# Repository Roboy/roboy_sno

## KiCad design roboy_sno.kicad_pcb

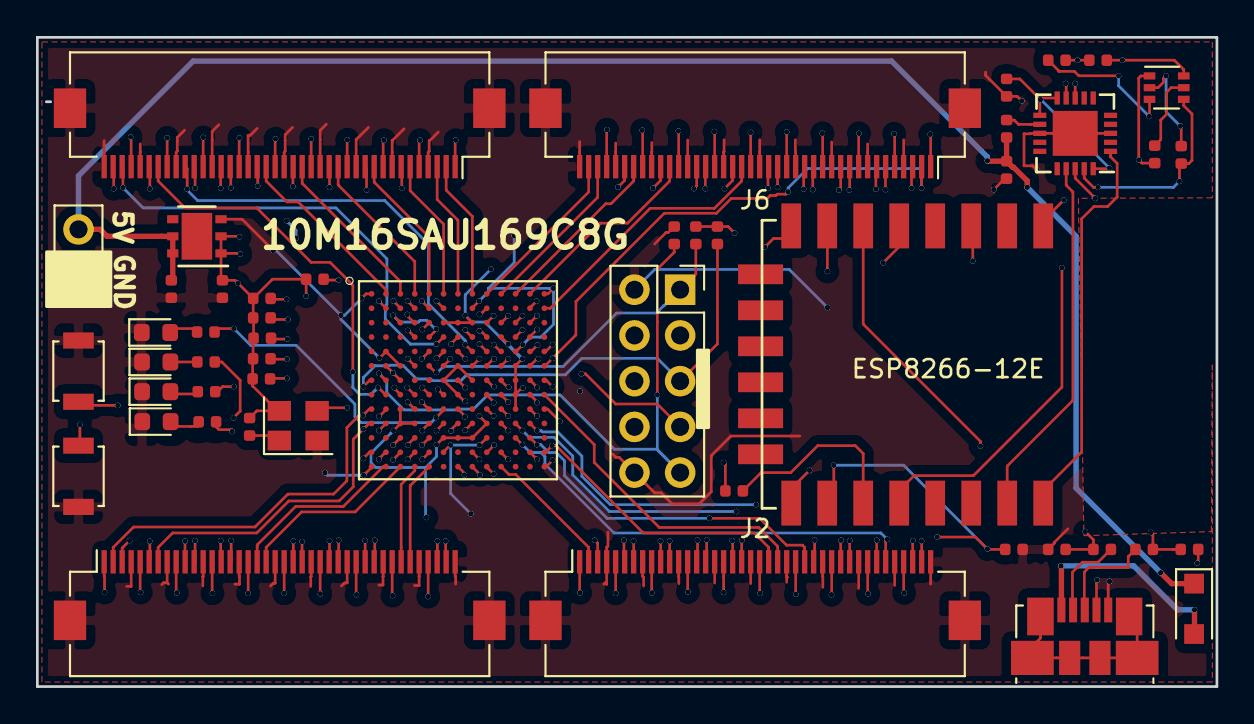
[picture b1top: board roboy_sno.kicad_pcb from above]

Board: 4 copper layers, 65.5 x 36.1 mm, 49 parts (0 on the bottom side), 126 nets.

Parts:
C2, C6: 10uF; C_0402_1005Metric
C8, C11: 47pF; C_0402_1005Metric
C9: 10n; C_0402_1005Metric
C10: 100n; C_0402_1005Metric
D1: D_Schottky; D_SOD-123F
D6, D7, D8, D9: LED; LED_0603_1608Metric
J1, J2, J3, J6: Conn_02x20_Odd_Even_MountingPin; Hirose_FH12-40S-0.5SH_1x40-1MP_P0.50mm_Horizontal
J4: Conn_02x05_Odd_Even; PinSocket_2x05_P2.54mm_Vertical
J5: Conn_01x02_Male; PinHeader_1x02_P2.54mm_Vertical
J7: USB_B_Mini; USB_Micro-B_Molex_47346-0001
L1: Ferrite_Bead; L_0402_1005Metric
Q1: Q_DUAL_NPN_NPN_E1B1C2E2B2C1; SOT-363_SC-70-6
R1, R3, R6, R24, R25, R26, R27: 1k; R_0402_1005Metric
R2, R4, R5, R7, R8, R10, R11, R12, R13, R16, R17, R18, R19: 10k; R_0402_1005Metric
R14, R15: 27; R_0402_1005Metric
SW1, SW2: SW_Push; SW_SPST_B3U-1000P
U1: LD39200; DFN-6-1EP_3x3mm_Pitch0.95mm
U2: DSC6083CE2A-032K768; Oscillator_SMD_Abracon_ASE-4Pin_3.2x2.5mm
U3: 10M16SAU169C8G; BGA169CP80_13X13_1100X1100X95B40N
U4: ESP8266-ESP-12E; ESP-12E_SMD
U5: FT231XQ-T; QFN-20-1EP_4x4mm_Pitch0.5mm

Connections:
3.3V: C2.2, J1.1, J1.5, J1.9, J1.13, J1.17, J1.21, J1.25, J1.29, J1.33, J1.37, J2.1, J2.5, J2.9, J2.13, J2.17, J2.21, J2.25, J2.29, J2.33, J2.37, J3.1, J3.5, J3.9, J3.13, J3.17, J3.21, J3.25, J3.29, J3.33, J3.37, J4.8, J6.1, J6.5, J6.9, J6.13, J6.17, J6.21, J6.25, J6.29, J6.33, J6.37, R1.2, R2.1, R3.2, R4.1, R5.1, R7.1, R8.1, R12.1, R13.1, R16.1, R17.1, R18.2, U1.1, U1.2, U2.4, U3.C6, U3.C7, U3.C8, U3.D4, U3.D10, U3.F2, U3.F7, U3.F11, U3.G3, U3.G6, U3.G8, U3.G11, U3.H7, U3.H11, U3.J3, U3.J11, U3.K3, U3.K4, U3.K9, U3.L6, U3.L7, U3.L8, U4.8
/A2: J3.22, U3.A2
/A3: J3.18, U3.A3
/A4: J3.14, U3.A4
/A5: J3.10, U3.A5
/A6: J3.6, U3.A6
/A7: J3.3, U3.A7
/A8: J3.2, U3.A8
/A9: J6.39, U3.A9
/A10: J6.38, U3.A10
/A11: J6.34, U3.A11
/A12: J6.30, U3.A12
/B2: J3.23, U3.B2
/B3: J3.19, U3.B3
/B4: J3.15, U3.B4
/B5: J3.11, U3.B5
/B6: J3.7, U3.B6
/B12: J6.27, U3.B12
/B13: J6.22, U3.B13
/C9: J6.35, U3.C9
/C10: J6.31, U3.C10
/C11: J6.23, U3.C11
/C12: J6.19, U3.C12
/D6: J3.38, U3.D6
/D8: J3.27, U3.D8
/D9: J3.26, U3.D9
/D11: J6.26, U3.D11
/D12: J6.15, U3.D12
/E6: J3.39, U3.E6
/E8: J3.31, U3.E8
/E9: J3.30, U3.E9
/E10: J6.6, U3.E10
/E12: J6.7, U3.E12
/E13: J6.10, U3.E13
/ESP8266-12E/GPIO2: R18.1, U4.17
/F4: J3.35, U3.F4
/F8: J6.18, U3.F8
/F9: J6.14, U3.F9
/F10: J6.11, U3.F10
/F12: J6.3, U3.F12
/F13: J6.2, U3.F13
/G9: J2.18, U3.G9
/G10: J2.19, U3.G10
/G12: J2.38, U3.G12
/G13: J2.39, U3.G13
/H2: J3.34, U3.H2
/H3: J1.3, U3.H3
/H4: SW2.2, U3.H4
/H5: SW1.2, U3.H5
/H9: J2.10, U3.H9
/H10: J2.11, U3.H10
/H13: J2.23, U3.H13
/J1: J1.2, U3.J1
/J2: J1.6, U3.J2
/J5: R27.1, U3.J5
/J6: R26.1, U3.J6
/J7: J1.38, U3.J7
/J9: J2.6, U3.J9
/J10: J2.7, U3.J10
/J12: J2.34, U3.J12
/J13: J2.31, U3.J13
/K1: J1.7, U3.K1
/K2: J1.10, U3.K2
/K5: J1.11, U3.K5
/K6: J1.14, U3.K6
/K7: J1.15, U3.K7
/K8: J1.39, U3.K8
/K10: J2.15, U3.K10
/K11: J2.27, U3.K11
/K12: J2.30, U3.K12
/L3: J1.22, U3.L3
/L4: J1.23, U3.L4
/L5: J1.27, U3.L5
/L11: J2.35, U3.L11
/L12: J2.26, U3.L12
/M1: R25.1, U3.M1
/M2: R24.1, U3.M2
/M3: J1.26, U3.M3
/M4: J1.30, U3.M4
/M5: J1.31, U3.M5
/M10: J2.3, U3.M10
/M12: J2.14, U3.M12
/M13: J2.22, U3.M13
/N2: J1.18, U3.N2
/N3: J1.19, U3.N3
/N4: J1.34, U3.N4
/N5: J1.35, U3.N5
/N10: J2.2, U3.N10
/TCK: J4.9, R6.1, U3.G2
/TDI: J4.1, R16.2, U3.F5
/TDO: J4.7, U3.F6
/TMS: J4.5, R17.2, U3.G1
DTR: Q1.1, R11.1, U5.18
ESP_EN: U3.N9, U4.3
GND: C2.1, C6.1, C8.1, C9.1, C10.2, C11.1, D6.1, D7.1, D8.1, D9.1, J1.4, J1.8, J1.12, J1.16, J1.20, J1.24, J1.28, J1.32, J1.36, J1.40, J1.MP, J2.4, J2.8, J2.12, J2.16, J2.20, J2.24, J2.28, J2.32, J2.36, J2.40, J2.MP, J3.4, J3.8, J3.12, J3.16, J3.20, J3.24, J3.28, J3.32, J3.36, J3.40, J3.MP, J4.2, J4.10, J5.1, J6.4, J6.8, J6.12, J6.16, J6.20, J6.24, J6.28, J6.32, J6.36, J6.40, J6.MP, J7.4, J7.5, R6.2, R19.2, SW1.1, SW2.1, U1.3, U2.2, U3.A1, U3.A13, U3.B8, U3.C3, U3.D5, U3.E2, U3.E11, U3.F3, U3.G7, U3.H12, U3.J4, U3.L9, U3.M6, U3.N1, U3.N13, U4.15, U5.3, U5.13, U5.21
GPIO0: Q1.6, R12.2, U4.18
unnamed: C8.2, R15.2, U5.8
unnamed: C10.1, U5.10, U5.11, U5.20
unnamed: C11.2, R14.2, U5.9
unnamed: D1.2, J7.1
unnamed: D6.2, R24.2
unnamed: D7.2, R25.2
unnamed: D8.2, R26.2
unnamed: D9.2, R27.2
unnamed: J7.2, R14.1
unnamed: J7.3, R15.1
unnamed: L1.2, U5.12
unnamed: Q1.2, R10.2
unnamed: Q1.5, R11.2
unnamed: R1.1, U3.C5
unnamed: R2.2, U3.E7
unnamed: R3.1, U3.C4
unnamed: R4.2, U3.D7
unnamed: R7.2, U3.E5
unnamed: R8.2, U2.1
unnamed: U2.3, U3.H6
unnamed: U4.21, U5.17
unnamed: U4.22, U5.1
RESET: Q1.3, R13.2, U4.1
RESET_N: R5.2, U3.B9
RTS: Q1.4, R10.1, U5.19
SPI_CLK: U3.M9, U4.5
SPI_CSO: R19.1, U3.M8, U4.16
SPI_MISO: U3.N8, U4.6
SPI_MOSI: U3.N7, U4.7
VDD5V: C6.2, C9.2, D1.1, J5.2, L1.1, U1.5, U1.6

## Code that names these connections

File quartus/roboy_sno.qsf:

# -------------------------------------------------------------------------- #
#
# Copyright (C) 2017  Intel Corporation. All rights reserved.
# Your use of Intel Corporation's design tools, logic functions 
# and other software and tools, and its AMPP partner logic 
# functions, and any output files from any of the foregoing 
# (including device programming or simulation files), and any 
# associated documentation or information are expressly subject 
# to the terms and conditions of the Intel Program License 
# Subscription Agreement, the Intel Quartus Prime License Agreement,
# the Intel FPGA IP License Agreement, or other applicable license
# agreement, including, without limitation, that your use is for
# the sole purpose of programming logic devices manufactured by
# Intel and sold by Intel or its authorized distributors.  Please
# refer to the applicable agreement for further details.
#
# -------------------------------------------------------------------------- #
#
# Quartus Prime
# Version 17.1.0 Build 590 10/25/2017 SJ Lite Edition
# Date created = 21:33:24  Juli 25, 2018
#
# -------------------------------------------------------------------------- #
#
# Notes:
#
# 1) The default values for assignments are stored in the file:
#		roboy_sno_assignment_defaults.qdf
#    If this file doesn't exist, see file:
#		assignment_defaults.qdf
#
# 2) Altera recommends that you do not modify this file. This
#    file is updated automatically by the Quartus Prime software
#    and any changes you make may be lost or overwritten.
#
# -------------------------------------------------------------------------- #


set_global_assignment -name FAMILY "MAX 10"
set_global_assignment -name DEVICE 10M16SAU169C8G
set_global_assignment -name TOP_LEVEL_ENTITY roboy_sno
set_global_assignment -name ORIGINAL_QUARTUS_VERSION 17.1.0
set_global_assignment -name PROJECT_CREATION_TIME_DATE "21:33:24  JULI 25, 2018"
set_global_assignment -name LAST_QUARTUS_VERSION "18.0.0 Lite Edition"
set_global_assignment -name PROJECT_OUTPUT_DIRECTORY output_files
set_global_assignment -name MIN_CORE_JUNCTION_TEMP 0
set_global_assignment -name MAX_CORE_JUNCTION_TEMP 85
set_global_assignment -name ERROR_CHECK_FREQUENCY_DIVISOR 256
set_global_assignment -name EDA_SIMULATION_TOOL "ModelSim-Altera (Verilog)"
set_global_assignment -name EDA_TIME_SCALE "1 ps" -section_id eda_simulation
set_global_assignment -name EDA_OUTPUT_DATA_FORMAT "VERILOG HDL" -section_id eda_simulation
set_location_assignment PIN_C10 -to D[0]
set_location_assignment PIN_C9 -to E[0]
set_location_assignment PIN_A8 -to D[1]
set_location_assignment PIN_A9 -to E[1]
set_location_assignment PIN_A10 -to D[2]
set_location_assignment PIN_A11 -to E[2]
set_location_assignment PIN_D8 -to D[3]
set_location_assignment PIN_E8 -to E[3]
set_location_assignment PIN_A7 -to D[4]
set_location_assignment PIN_A6 -to E[4]
set_location_assignment PIN_B6 -to D[5]
set_location_assignment PIN_B5 -to E[5]
set_location_assignment PIN_A5 -to D[6]
set_location_assignment PIN_A4 -to E[6]
set_location_assignment PIN_E6 -to D[7]
set_location_assignment PIN_D6 -to E[7]
set_location_assignment PIN_B3 -to D[8]
set_location_assignment PIN_B4 -to E[8]
set_location_assignment PIN_A2 -to D[9]
set_location_assignment PIN_B2 -to E[9]
set_location_assignment PIN_D11 -to D[10]
set_location_assignment PIN_E10 -to E[11]
set_location_assignment PIN_D12 -to E[10]
set_location_assignment PIN_D9 -to D[11]
set_location_assignment PIN_A12 -to D[12]
set_location_assignment PIN_B13 -to E[12]
set_location_assignment PIN_C11 -to D[13]
set_location_assignment PIN_C12 -to E[13]
set_location_assignment PIN_B11 -to D[14]
set_location_assignment PIN_B12 -to E[14]
set_location_assignment PIN_E9 -to D[15]
set_location_assignment PIN_F8 -to E[15]
set_location_assignment PIN_F10 -to D[16]
set_location_assignment PIN_F9 -to E[16]
set_location_assignment PIN_E12 -to D[17]
set_location_assignment PIN_F12 -to E[17]
set_location_assignment PIN_E13 -to D[18]
set_location_assignment PIN_F13 -to E[18]
set_location_assignment PIN_G10 -to D[19]
set_location_assignment PIN_G9 -to E[19]
set_location_assignment PIN_J10 -to D[20]
set_location_assignment PIN_K10 -to E[20]
set_location_assignment PIN_L12 -to D[21]
set_location_assignment PIN_K11 -to E[21]
set_location_assignment PIN_J12 -to D[22]
set_location_assignment PIN_K12 -to E[22]
set_location_assignment PIN_H10 -to D[23]
set_location_assignment PIN_J9 -to E[23]
set_location_assignment PIN_H13 -to D[24]
set_location_assignment PIN_J13 -to E[24]
set_location_assignment PIN_H8 -to D[25]
set_location_assignment PIN_H9 -to E[25]
set_location_assignment PIN_G12 -to D[26]
set_location_assignment PIN_G13 -to E[26]
set_location_assignment PIN_L10 -to D[27]
set_location_assignment PIN_M10 -to E[27]
set_location_assignment PIN_K8 -to D[28]
set_location_assignment PIN_J8 -to E[28]
set_location_assignment PIN_L11 -to D[29]
set_location_assignment PIN_M11 -to E[29]
set_location_assignment PIN_M12 -to D[30]
set_location_assignment PIN_M13 -to E[30]
set_location_assignment PIN_K7 -to D[31]
set_location_assignment PIN_J7 -to E[31]
set_location_assignment PIN_K6 -to D[32]
set_location_assignment PIN_J6 -to E[32]
set_location_assignment PIN_M7 -to D[33]
set_location_assignment PIN_N6 -to E[33]
set_location_assignment PIN_J5 -to D[34]
set_location_assignment PIN_K5 -to E[34]
set_location_assignment PIN_L4 -to D[35]
set_location_assignment PIN_L5 -to E[35]
set_location_assignment PIN_N9 -to D[36]
set_location_assignment PIN_N10 -to E[36]
set_location_assignment PIN_M9 -to D[37]
set_location_assignment PIN_M8 -to E[37]
set_location_assignment PIN_K2 -to D[38]
set_location_assignment PIN_K1 -to E[38]
set_location_assignment PIN_L3 -to D[39]
set_location_assignment PIN_M3 -to E[39]
set_location_assignment PIN_N3 -to D[40]
set_location_assignment PIN_N2 -to E[40]
set_location_assignment PIN_M2 -to D[41]
set_location_assignment PIN_M1 -to E[41]
set_location_assignment PIN_H4 -to D[42]
set_location_assignment PIN_H5 -to E[42]
set_location_assignment PIN_M4 -to SPI_MOSI
set_location_assignment PIN_M5 -to SPI_MISO
set_location_assignment PIN_N4 -to SPI_CSO
set_location_assignment PIN_N5 -to SPI_CLK
set_location_assignment PIN_N7 -to ESP_EN
set_global_assignment -name PARTITION_NETLIST_TYPE SOURCE -section_id Top
set_global_assignment -name PARTITION_FITTER_PRESERVATION_LEVEL PLACEMENT_AND_ROUTING -section_id Top
set_global_assignment -name PARTITION_COLOR 16764057 -section_id Top
set_global_assignment -name POWER_PRESET_COOLING_SOLUTION "23 MM HEAT SINK WITH 200 LFPM AIRFLOW"
set_global_assignment -name POWER_BOARD_THERMAL_MODEL "NONE (CONSERVATIVE)"
set_global_assignment -name FLOW_ENABLE_POWER_ANALYZER ON
set_global_assignment -name POWER_DEFAULT_INPUT_IO_TOGGLE_RATE "12.5 %"
set_location_assignment PIN_J1 -to LED[0]
set_location_assignment PIN_J2 -to LED[1]
set_global_assignment -name IP_SEARCH_PATHS /home/letrend/workspace/roboy_sno/quartus/roboy_fpga_code/roboy_fpga_code/lighthouse_tracking
set_location_assignment PIN_A3 -to BUTTON
set_instance_assignment -name WEAK_PULL_UP_RESISTOR ON -to BUTTON
set_location_assignment PIN_H6 -to CLK16MHz
set_global_assignment -name VERILOG_FILE roboy_fpga_code/edge_detect/altera_edge_detector.v
set_global_assignment -name VHDL_FILE roboy_fpga_code/roboy_fpga_code/myo_control/spi_master_slave/trunk/rtl/spi_master_slave/spi_master.vhd
set_global_assignment -name QIP_FILE darkroom/synthesis/darkroom.qip
set_global_assignment -name VERILOG_FILE roboy_fpga_code/roboy_fpga_code/lighthouse_tracking/uart_tx.v
set_global_assignment -name VERILOG_FILE roboy_fpga_code/roboy_fpga_code/lighthouse_tracking/ts4231.v
set_global_assignment -name VERILOG_FILE roboy_fpga_code/roboy_fpga_code/lighthouse_tracking/SpiControl_esp8266.v
set_global_assignment -name VHDL_FILE roboy_fpga_code/roboy_fpga_code/lighthouse_tracking/lighthouse_sensor.vhd
set_global_assignment -name VHDL_FILE roboy_fpga_code/roboy_fpga_code/lighthouse_tracking/lighthouse_ootx_decoder.vhdl
set_global_assignment -name VERILOG_FILE roboy_fpga_code/roboy_fpga_code/lighthouse_tracking/DarkRoomOOTXdecoder.v
set_global_assignment -name VERILOG_FILE roboy_fpga_code/roboy_fpga_code/lighthouse_tracking/DarkRoom.v
set_global_assignment -name VERILOG_FILE roboy_sno.v
set_global_assignment -name CDF_FILE Chain1.cdf
set_instance_assignment -name PARTITION_HIERARCHY root_partition -to | -section_id Top

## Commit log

2018-03-20 schematics almost done
2018-03-23 esp8266 almost done
2018-03-23 with datasheet
2018-03-25 almost done with layout
2018-03-25 done with layout
2018-07-04 new schematics
2018-07-04 new pcb layput draft
2018-07-05 schematics done
2018-07-05 with grb
2018-07-11 with readme
2018-07-25 with pin assigment
2018-07-26 bug fixes and user leds/buttons
2018-08-08 with led
2018-08-09 better
2018-08-09 seem to work
2018-08-10 with forced trigger
2018-08-11 revision 4 motherfucer
2018-08-12 almost done
2018-08-12 with imu and mic
